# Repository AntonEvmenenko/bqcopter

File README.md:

# Big DIY Quadcopter

This project is dedicated to the development of a DIY quadcopter and its remote controller. The hardware, firmware, and software have been developed from scratch.

## Project logs on YouTube

## Architecture

The quadcopter and the controller are both equipped with 2.4GHz radio transceivers. The controller consists of two parts:

1. An Android smartphone running an application that allows receiving and displaying telemetry data from the quadcopter, as well as adjusting quadcopter control system parameters such as PID controller coefficients
2. A custom Arduino-based board to which the smartphone is connected via Bluetooth. This board essentially serves as a data converter, transmitting information received via Bluetooth over the 2.4GHz radio, and vice versa

## Hardware

### Quadcopter

**MCU**: STM32F103  
**IMU**: GY80 (L3G4200d + ADXL345 + HMC5883 + BMP085)  
**Radio**: NRF24L01  
**ESC**: Chinese ESC with SimonK firmware  
**Motors**: SunnySky X2212-13 980KV  
**Frame**: Chinese noname one  

### Controller

**Based on**: Arduino Nano  
**Radio**: NRF24L01  
**Bluetooth**: HC-05  

## Firmware  

The firmware was developed from scratch in C, except for the IMU code, which was taken from [here](https://x-io.co.uk/open-source-imu-and-ahrs-algorithms/)

## Software

The software in this project is a custom application written in Java for Android. Here are a couple of screenshots of this application:

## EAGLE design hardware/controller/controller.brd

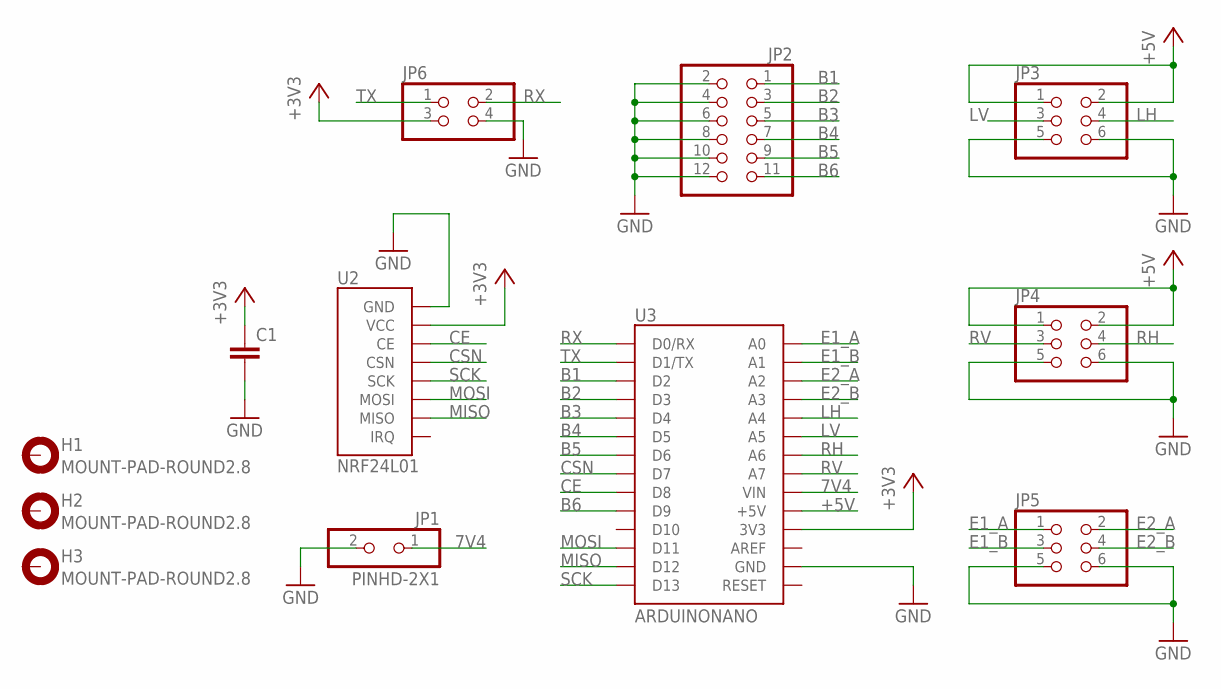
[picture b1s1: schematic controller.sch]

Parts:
C1: C-EUC0805; C0805
H1, H2, H3: MOUNT-PAD-ROUND2.8; 2,8-PAD
JP1: PINHD-2X1; 2X01/90
JP2: PINHD-2X6/90; 2X06/90
JP3, JP4, JP5: PINHD-2X3/90; 2X03/90
JP6: PINHD-2X2/90; 2X02/90
U2: NRF24L01
U3: ARDUINONANO; PDIP-32

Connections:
7V4: JP1.1, U3.VIN
+3V3: C1.1, JP6.3, U2.2 (VCC), U3.3V3
+5V: JP3.1, JP3.2, JP4.1, JP4.2, U3.+5V
B1: JP2.1, U3.D2
B2: JP2.3, U3.D3
B3: JP2.5, U3.D4
B4: JP2.7, U3.D5
B5: JP2.9, U3.D6
B6: JP2.11, U3.D9
CE: U2.3 (CE), U3.D8
CSN: U2.4 (CSN), U3.D7
E1_A: JP5.1, U3.A0
E1_B: JP5.3, U3.A1
E2_A: JP5.2, U3.A2
E2_B: JP5.4, U3.A3
GND: C1.2, JP1.2, JP2.2, JP2.4, JP2.6, JP2.8, JP2.10, JP2.12, JP3.5, JP3.6, JP4.5, JP4.6, JP5.5, JP5.6, JP6.4, U2.1 (GND), U3.GND, U3.GND1 (GND)
LH: JP3.4, U3.A4
LV: JP3.3, U3.A5
MISO: U2.7 (MISO), U3.D12
MOSI: U2.6 (MOSI), U3.D11
RH: JP4.4, U3.A6
RV: JP4.3, U3.A7
RX: JP6.2, U3.D0/RX
SCK: U2.5 (SCK), U3.D13
TX: JP6.1, U3.D1/TX

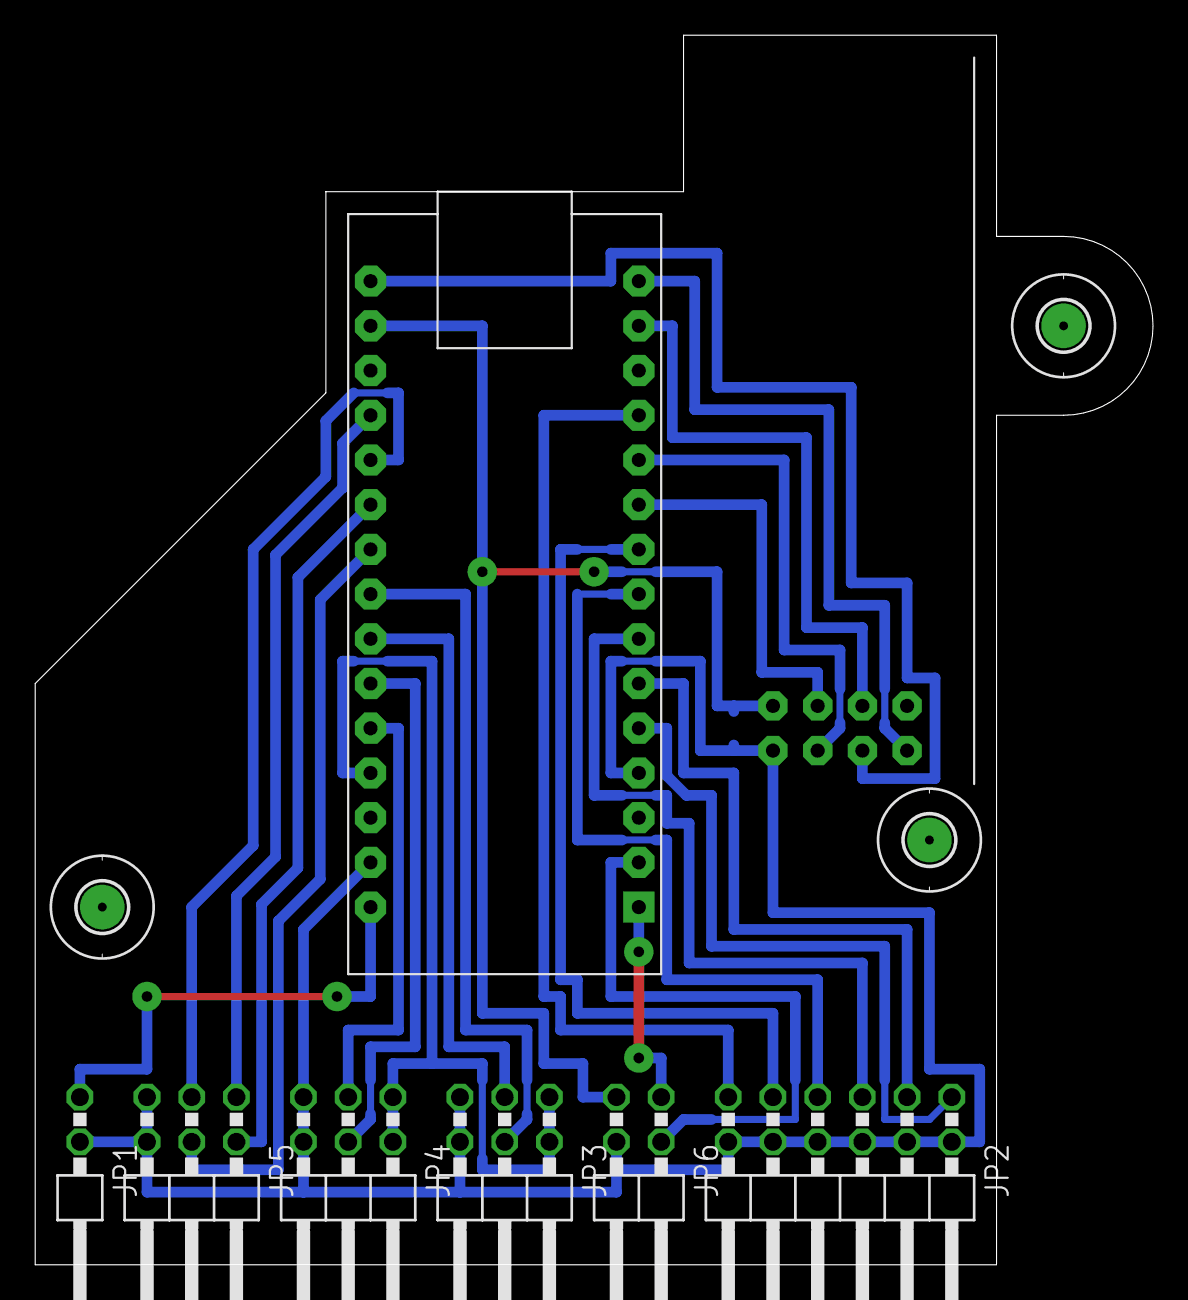
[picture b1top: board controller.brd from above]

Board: 2 copper layers, 63.5 x 69.8 mm, 12 parts (1 on the bottom side), 25 nets.

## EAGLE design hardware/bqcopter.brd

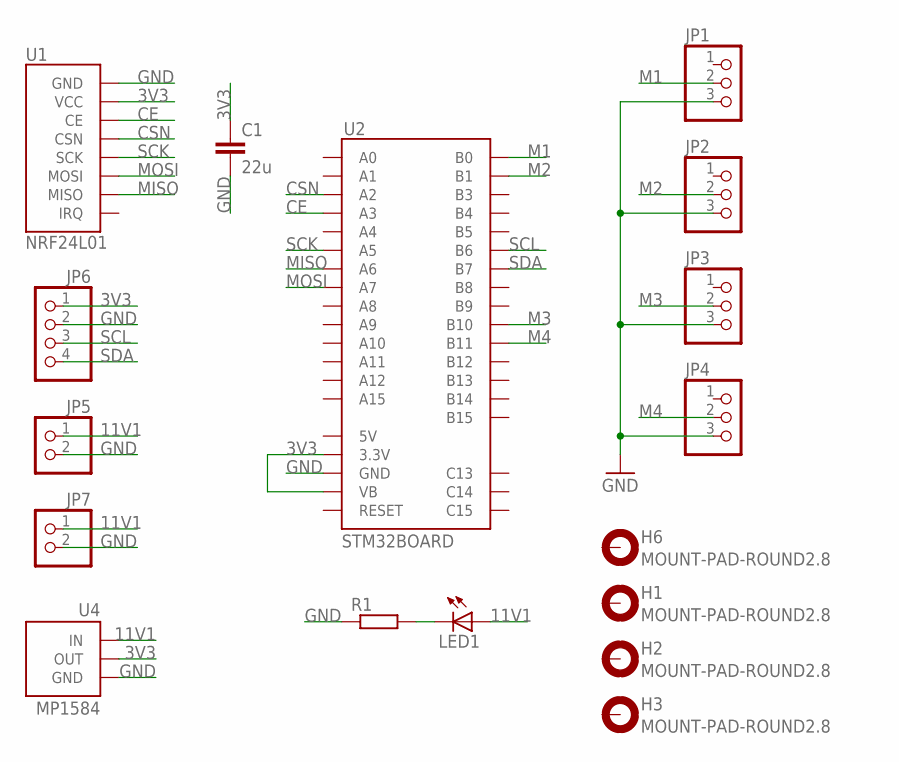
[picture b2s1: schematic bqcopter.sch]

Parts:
C1: 22u; C0805
H1, H2, H3, H6: MOUNT-PAD-ROUND2.8; 2,8-PAD
JP1, JP2, JP3, JP4: PINHD-1X3; 1X03
JP5, JP7: PINHD-1X2; 1X02
JP6: PINHD-1X4; 1X04
LED1: LED3MM
R1: R-EU_M0805; M0805
U1: NRF24L01
U2: STM32BOARD
U4: MP1584

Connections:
3V3: C1.1, JP6.1, U1.2 (VCC), U2.3.3V_1 (3.3V), U2.3.3V_2 (3.3V), U2.VB, U4.OUT+1 (OUT), U4.OUT+2 (OUT)
11V1: JP5.1, JP7.1, LED1.A, U4.IN+1 (IN), U4.IN+2 (IN)
CE: U1.3 (CE), U2.A3
CSN: U1.4 (CSN), U2.A2
GND: C1.2, JP1.3, JP2.3, JP3.3, JP4.3, JP5.2, JP6.2, JP7.2, R1.1, U1.1 (GND), U2.GND_1 (GND), U2.GND_2 (GND), U2.GND_3 (GND), U4.IN-1 (GND), U4.IN-2 (GND), U4.OUT-1 (GND), U4.OUT-2 (GND)
M1: JP1.2, U2.B0
M2: JP2.2, U2.B1
M3: JP3.2, U2.B10
M4: JP4.2, U2.B11
MISO: U1.7 (MISO), U2.A6
MOSI: U1.6 (MOSI), U2.A7
unnamed: LED1.K (C), R1.2
SCK: U1.5 (SCK), U2.A5
SCL: JP6.3, U2.B6
SDA: JP6.4, U2.B7

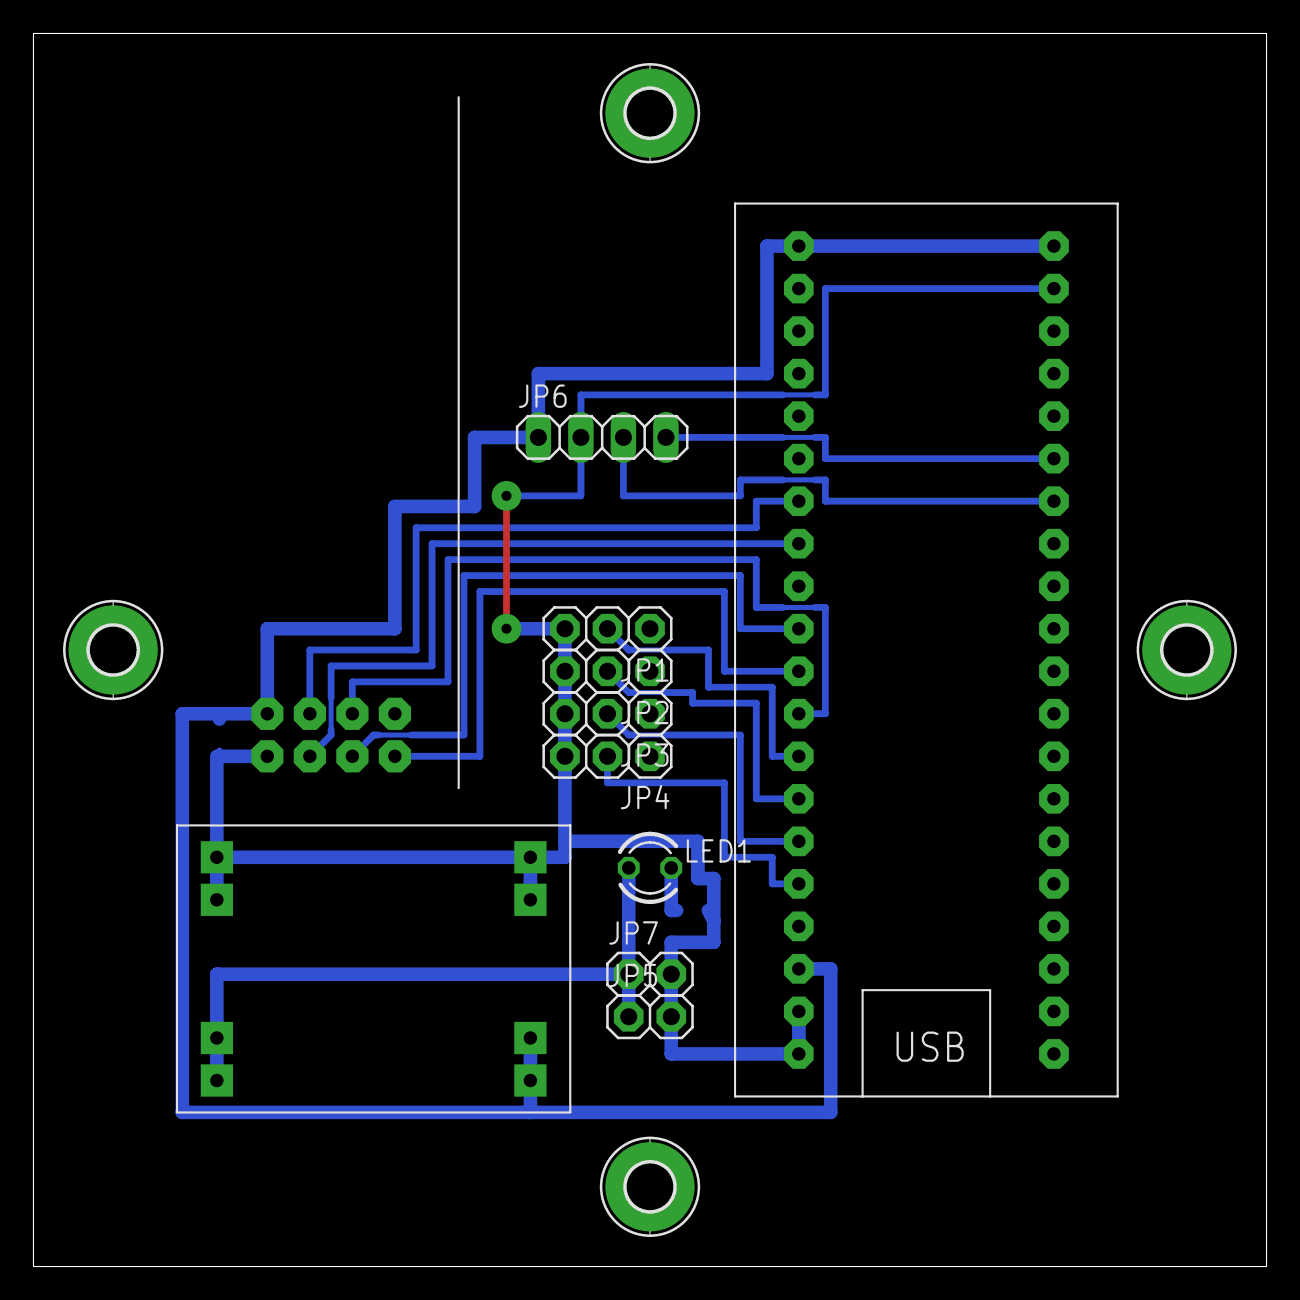
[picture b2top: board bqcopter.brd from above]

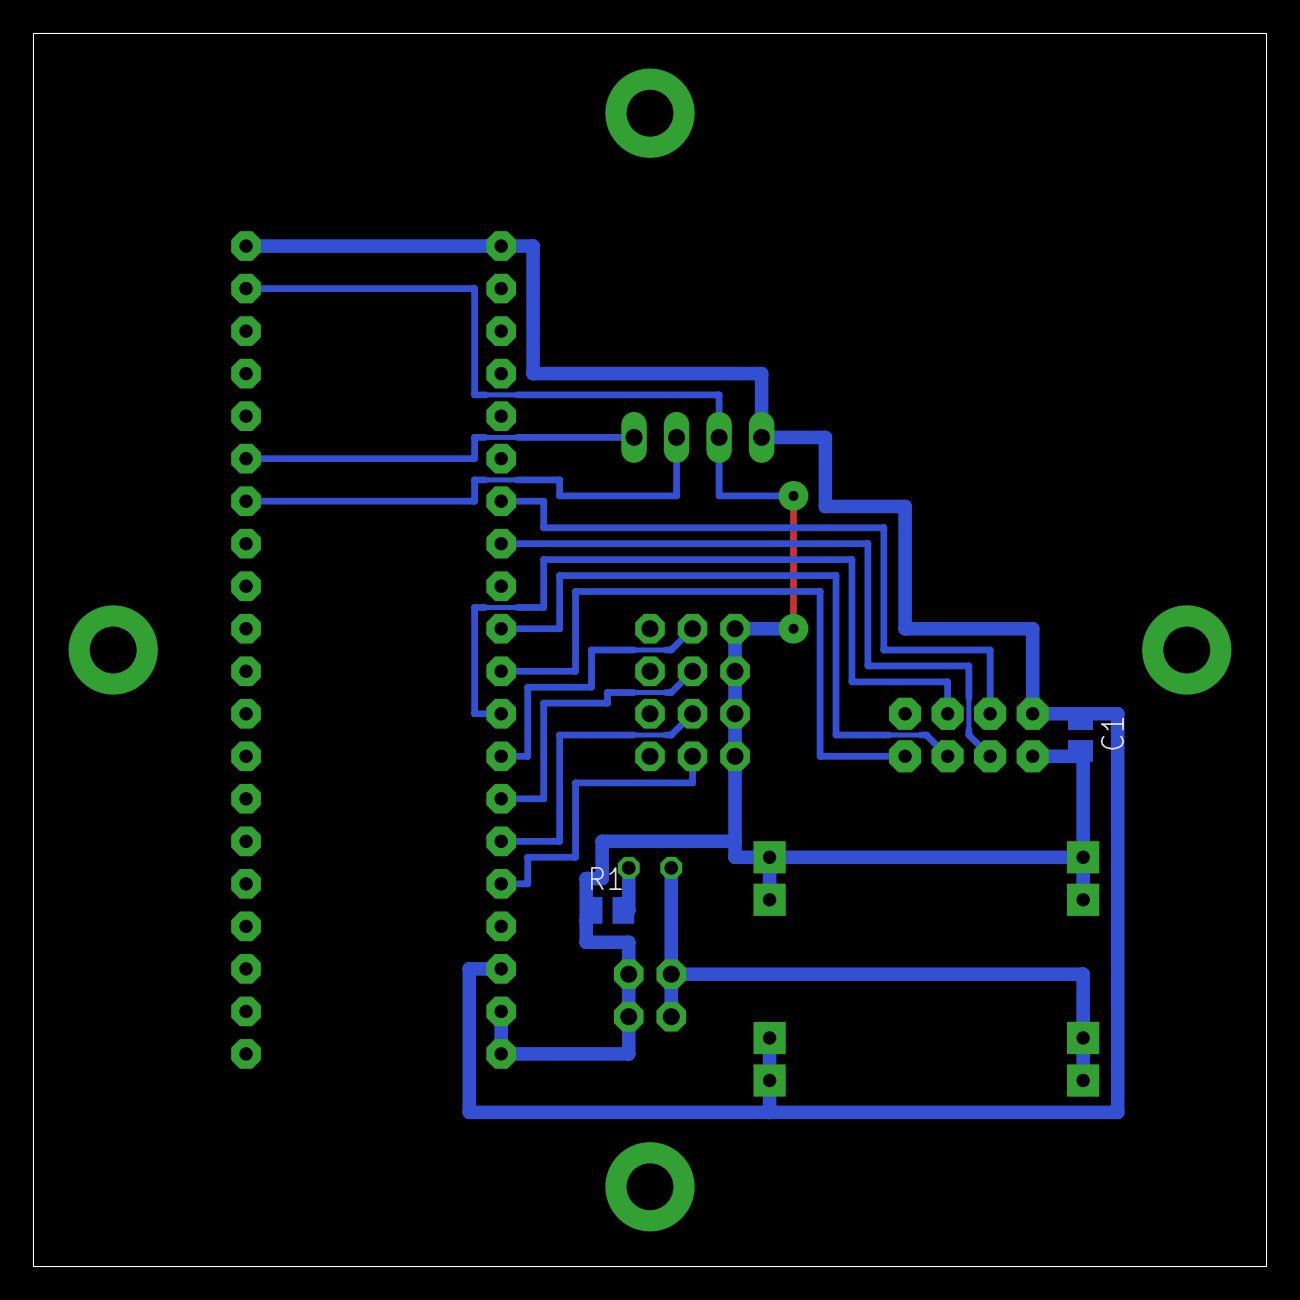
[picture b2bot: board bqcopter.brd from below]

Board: 2 copper layers, 73.7 x 73.7 mm, 17 parts (2 on the bottom side), 15 nets.

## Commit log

2018-03-22 bqcopter.png added
2018-03-22 bqcopter.png added to readme
2018-03-22 board.png added
2018-03-22 Description for bqcopter.png removed
2018-03-22 board.png updated
2018-03-22 android screenshots and photo of transmitter added
2018-03-22 transmitter.png updated
2018-03-22 diagram.png added
2018-03-22 controller_old.png added
2018-03-22 controller_new.jpg added
2023-06-03 README.md updated
2023-06-03 README.md updated more images added
2023-06-04 Android combined screenshot updated
2023-06-04 controller hw added
2023-06-06 Android app screenshot updated
